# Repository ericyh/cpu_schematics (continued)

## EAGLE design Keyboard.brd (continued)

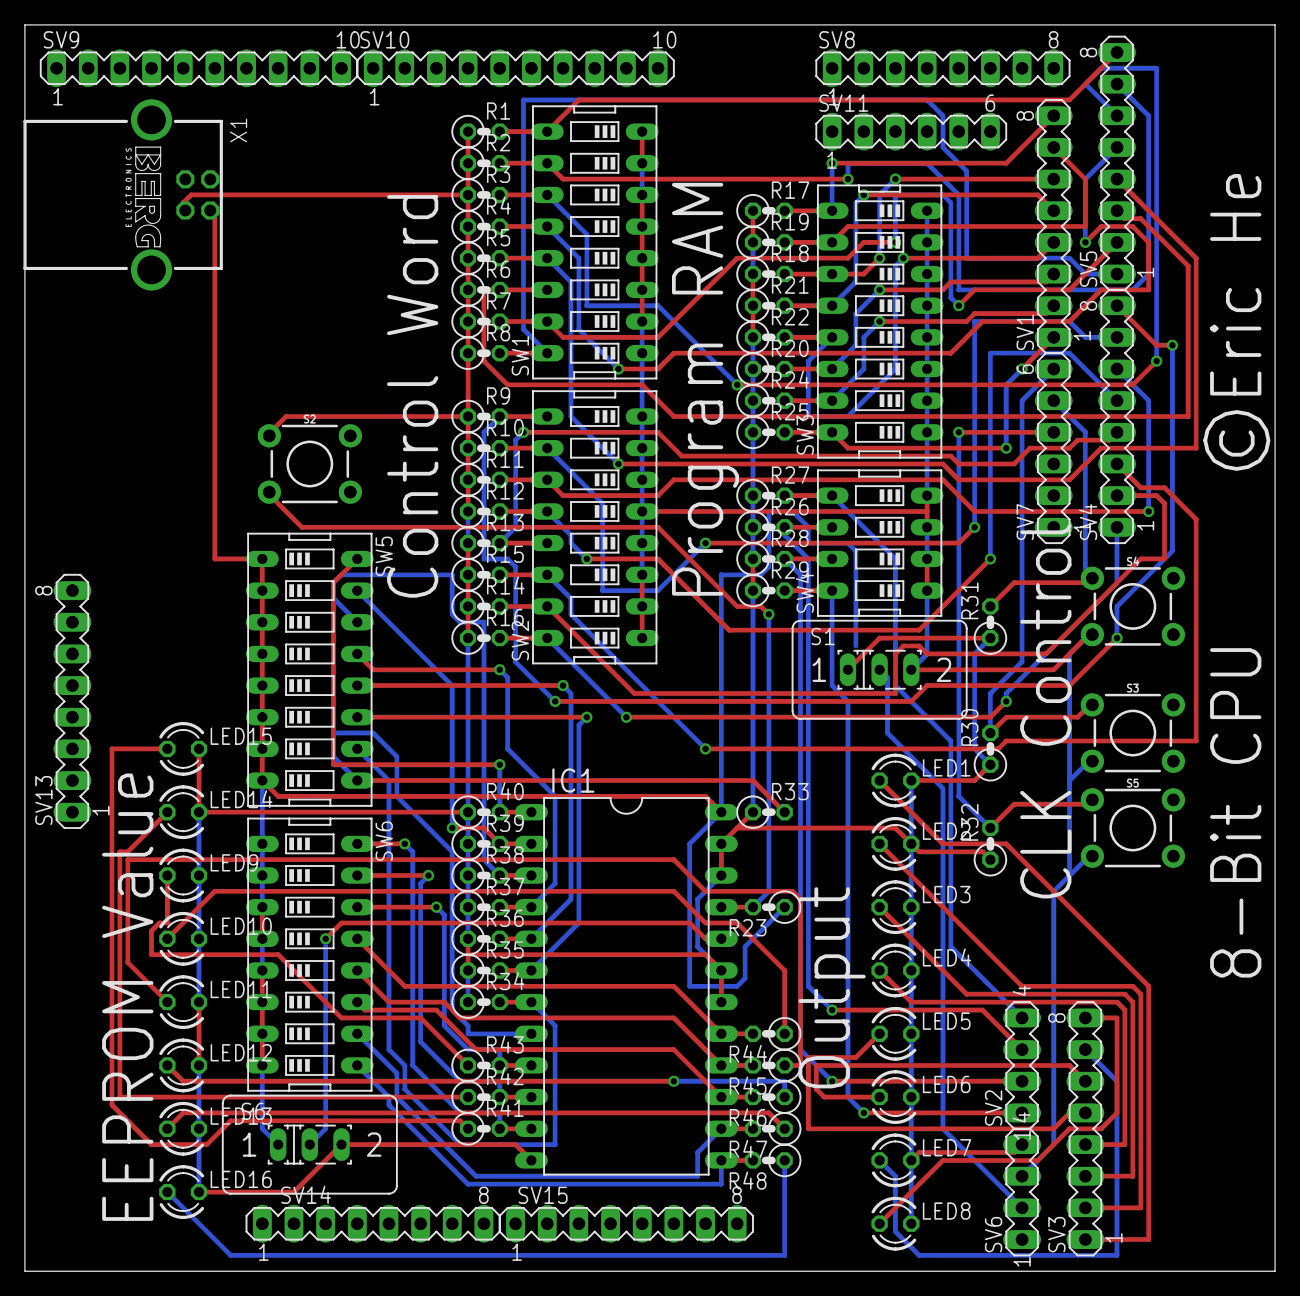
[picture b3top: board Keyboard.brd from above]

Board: 2 copper layers, 100.3 x 100.0 mm, 92 parts (0 on the bottom side), 68 nets.

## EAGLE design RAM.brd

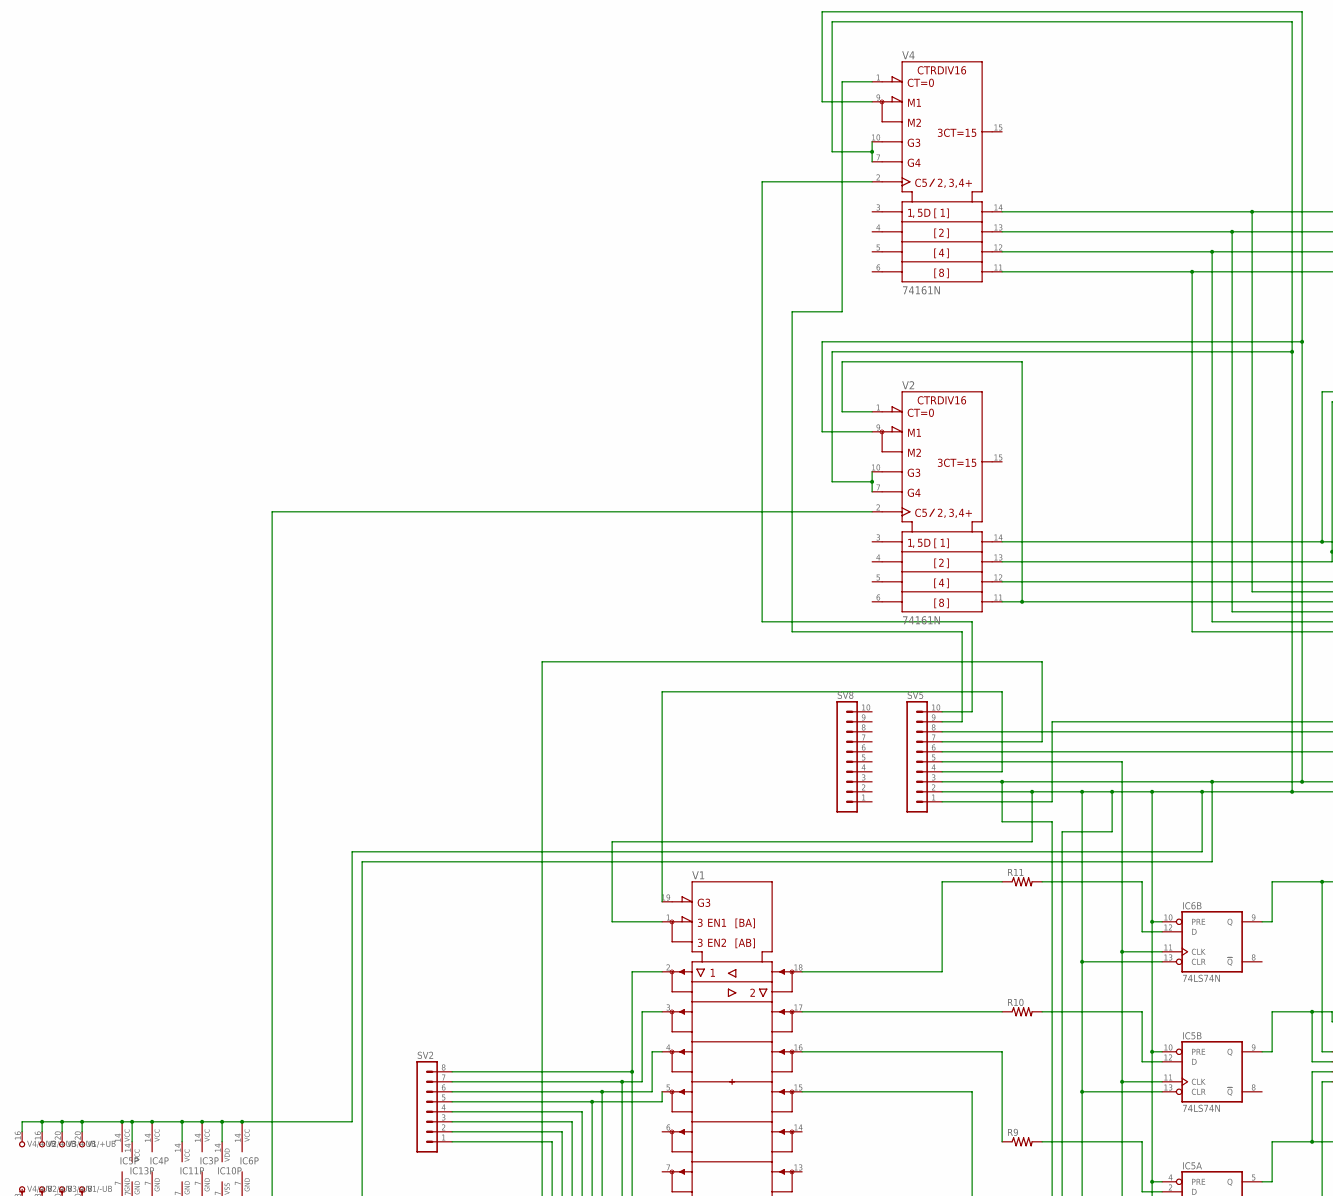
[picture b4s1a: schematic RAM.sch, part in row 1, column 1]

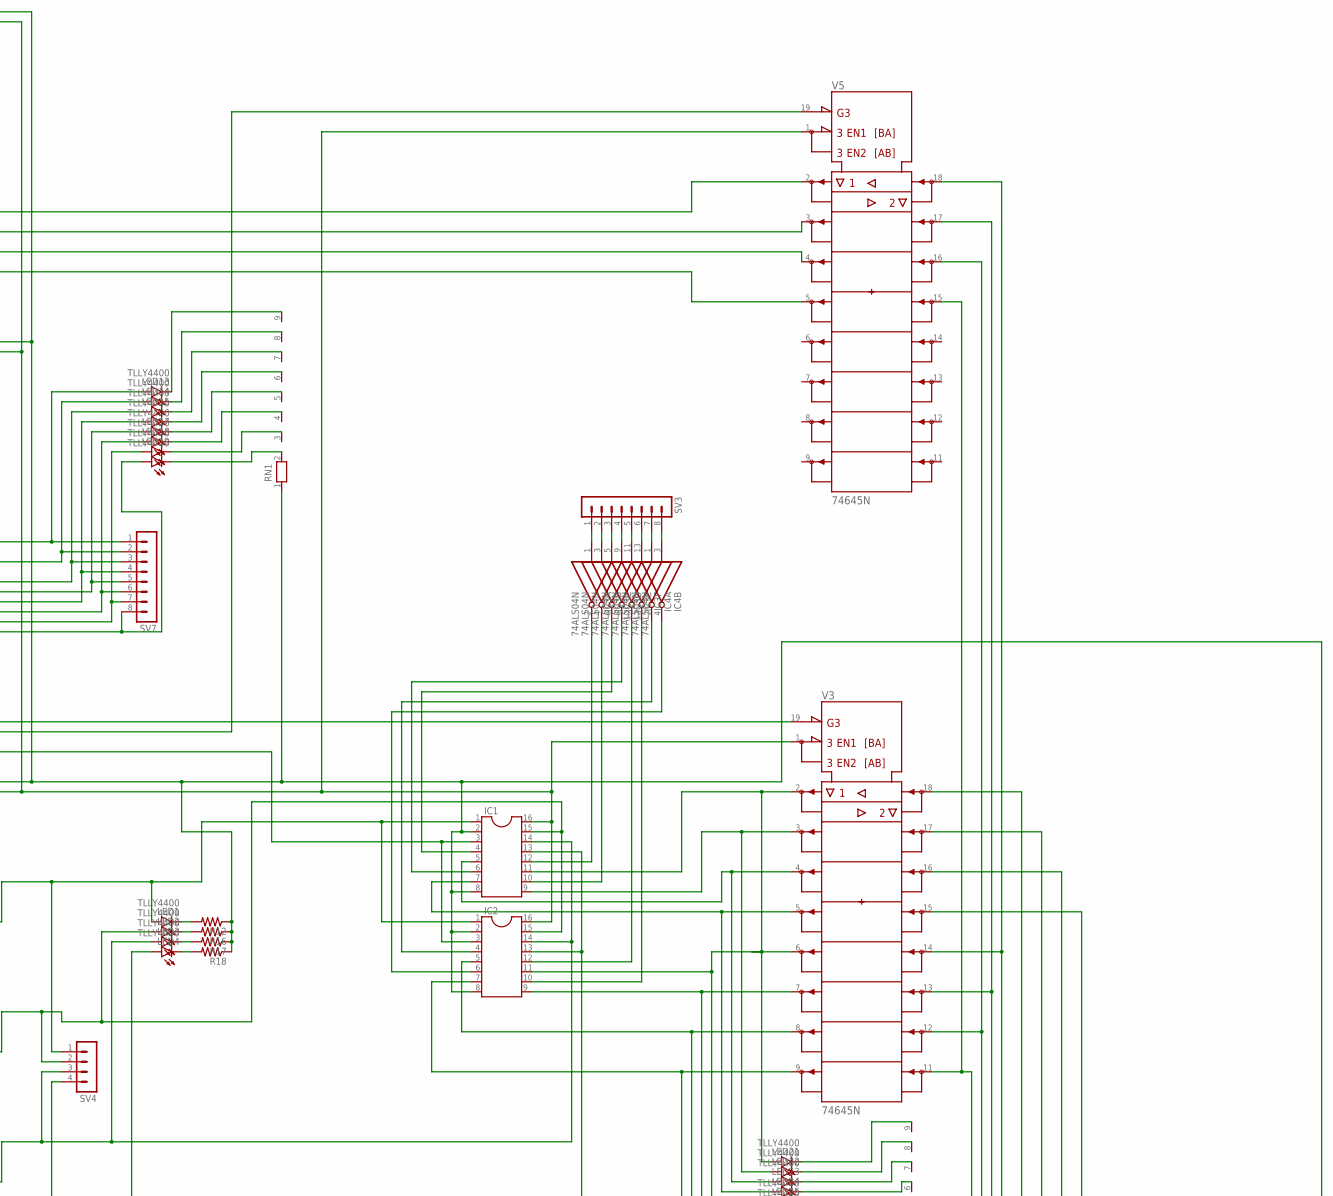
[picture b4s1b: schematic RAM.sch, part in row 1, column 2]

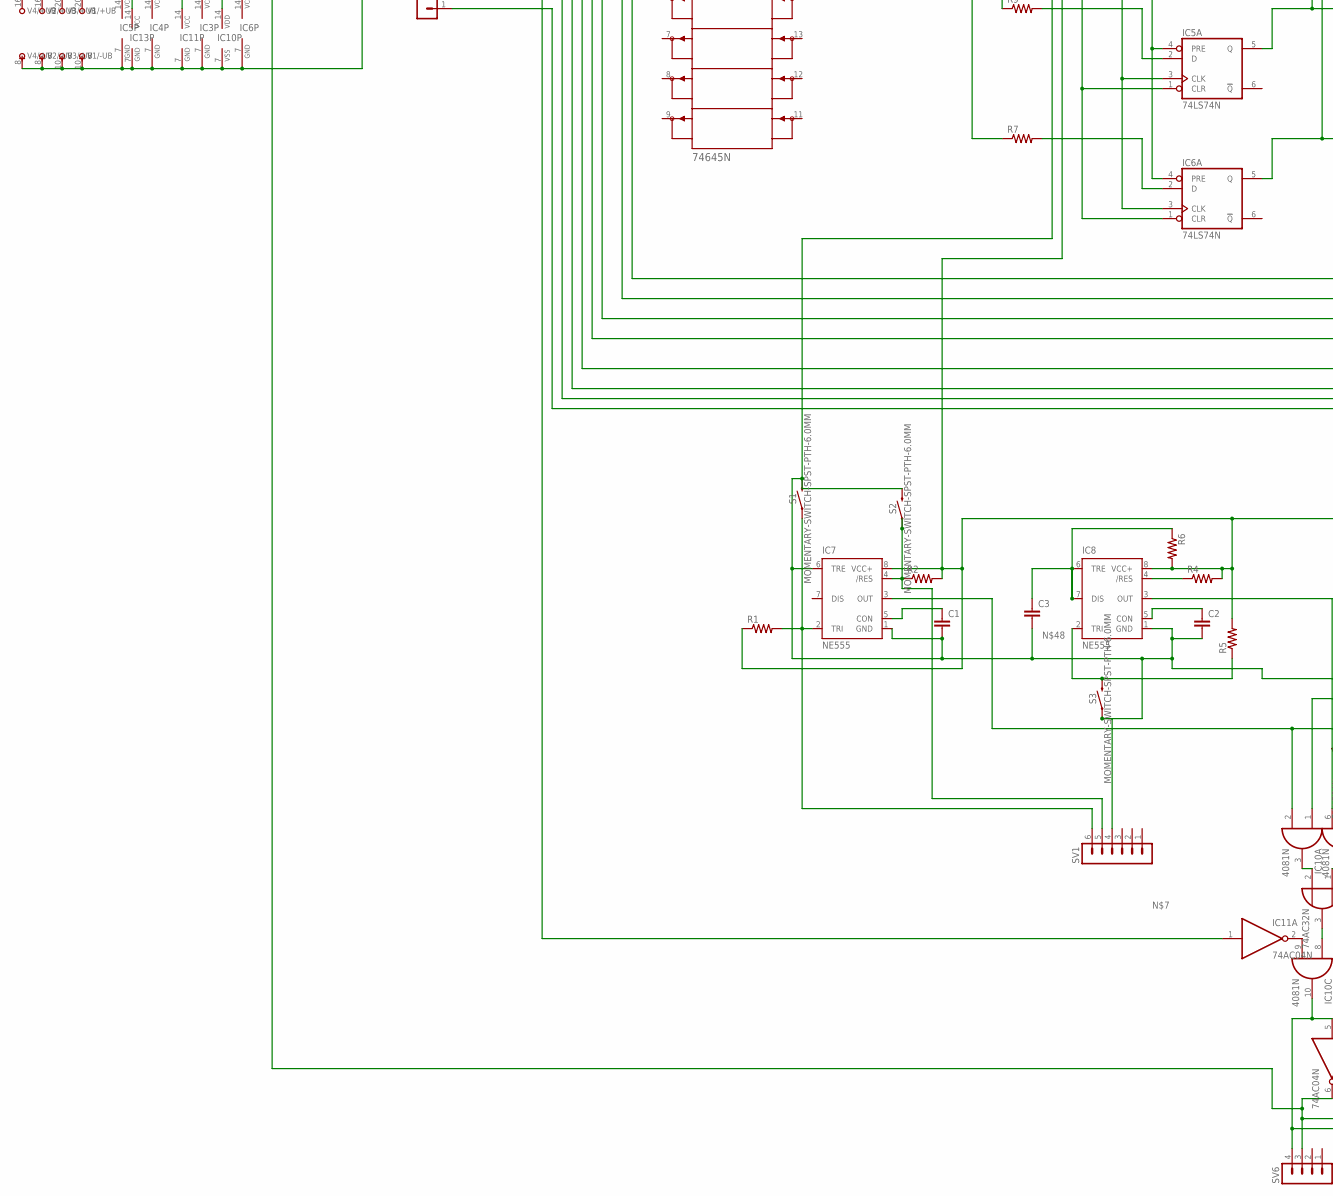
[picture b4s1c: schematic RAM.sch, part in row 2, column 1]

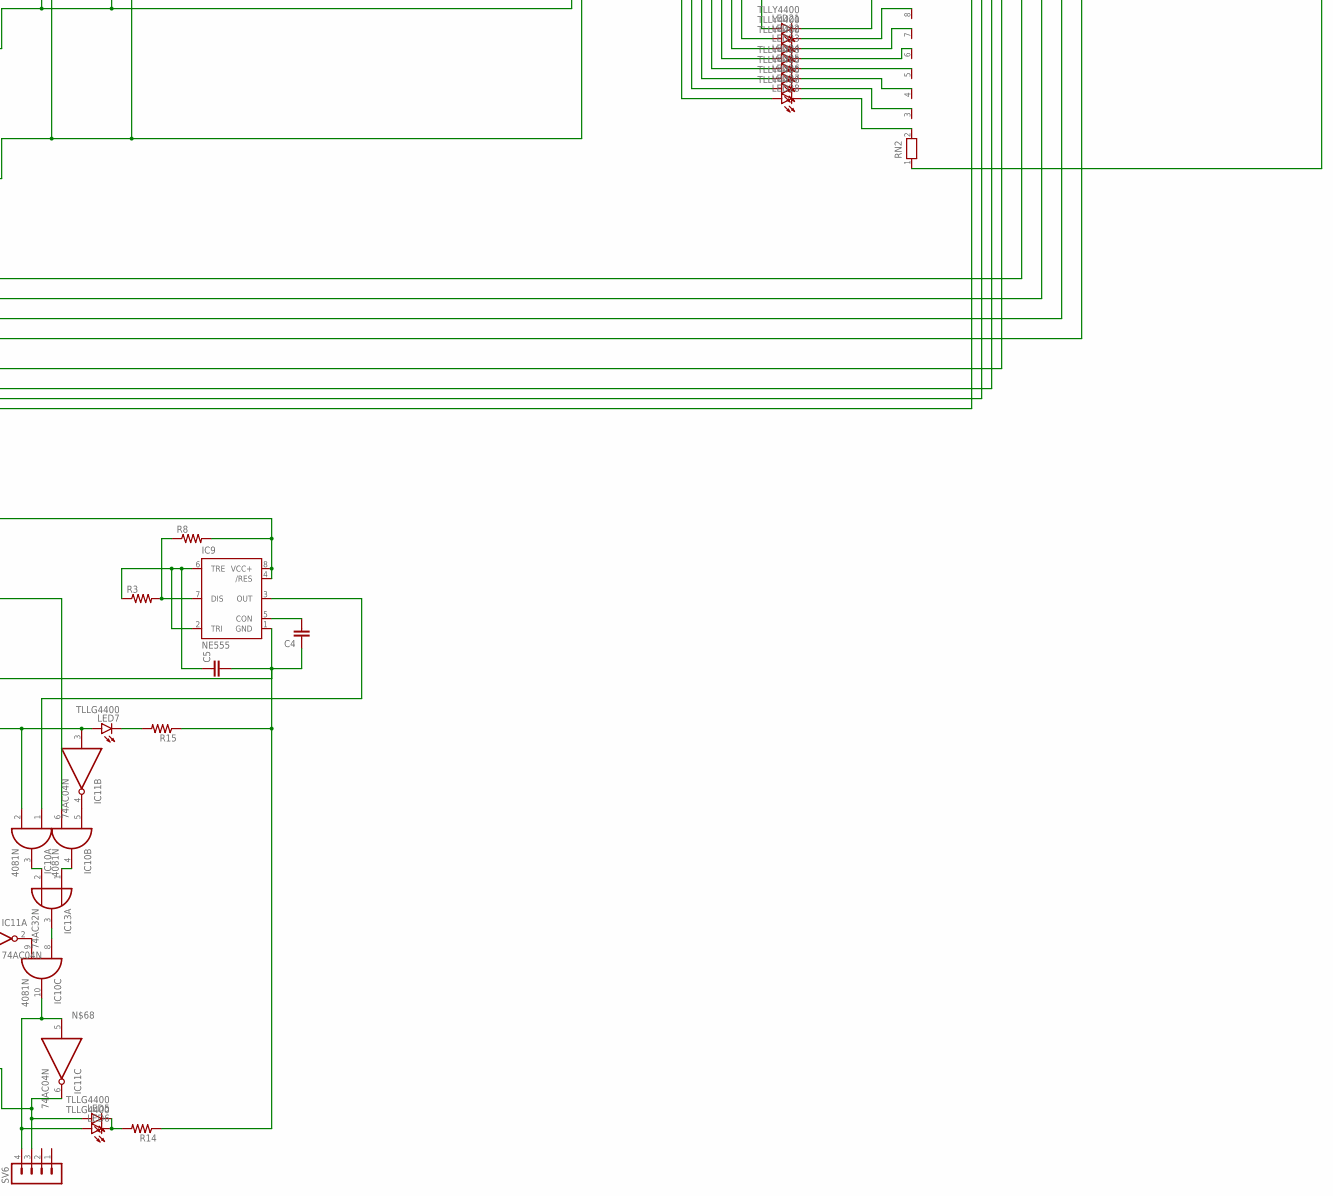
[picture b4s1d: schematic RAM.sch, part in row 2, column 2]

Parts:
C1, C2, C3, C4, C5: C2,5-3; C2.5-3
IC1, IC2: DIL16
IC3, IC4: 74ALS04N; DIL14
IC5, IC6: 74LS74N; DIL14
IC7, IC8, IC9: NE555; DIL-08
IC10: 4081N; DIL14
IC11: 74AC04N; DIL14
IC13: 74AC32N; DIL14
LED1, LED2, LED3, LED4, LED13, LED14, LED15, LED16, LED17, LED18, LED19, LED20, LED21, LED22, LED23, LED24, LED25, LED26, LED27, LED28: TLLY4400; LED3MM
LED5, LED6, LED7: TLLG4400; LED3MM
R1, R2, R3, R4, R5, R6, R7, R8, R9, R10, R11, R12, R14, R15, R16, R17, R18: R-US_0411/3V; 0411V
RN1, RN2: RN08; RN-9
S1, S2, S3: MOMENTARY-SWITCH-SPST-PTH-6.0MM; TACTILE_SWITCH_PTH_6.0MM
SV1: MA06-1
SV2, SV3, SV7: MA08-1
SV4, SV6: MA04-1
SV5, SV8: MA10-1
V1, V3, V5: 74645N; DIL20
V2, V4: 74161N; DIL16

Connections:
+UB: V5.20 (+UB)
-UB: V5.10 (-UB)
unnamed: LED28.K (C), RN2.2
unnamed: IC1.10, IC3.4 (O)
unnamed: IC1.1, IC2.1, IC6.9 (Q), LED1.A, SV4.1
unnamed: IC1.15, IC2.15, IC5.9 (Q), LED2.A, SV4.2
unnamed: C1.1, IC7.5 (CON)
unnamed: LED19.A, SV7.7, V4.12 (QC), V5.4 (A3)
unnamed: IC11.1 (I), SV5.7
unnamed: IC7.2 (TRI), R1.2, S1.1, SV1.6
unnamed: IC1.4, IC3.6 (O)
unnamed: SV2.8, V1.2 (A1), V3.18 (B1)
unnamed: IC1.3, IC2.3, SV5.6
unnamed: IC1.5, LED23.A, V3.4 (A3)
unnamed: IC1.7, LED24.A, V3.5 (A4)
unnamed: IC2.4, IC4.2 (O)
unnamed: IC2.10, IC3.12 (O)
unnamed: IC2.5, LED27.A, V3.8 (A7)
unnamed: IC2.7, LED28.A, V3.9 (A8)
unnamed: IC1.11, IC2.11, LED21.A, LED25.A, V3.2 (A1)
unnamed: IC5.3 (CLK), IC5.11 (CLK), IC6.3 (CLK), IC6.11 (CLK), SV5.5
unnamed: IC1.9, LED22.A, V3.3 (A2)
unnamed: IC1.6, IC3.8 (O)
unnamed: R10.1, V1.17 (B2)
unnamed: IC2.12, IC3.10 (O)
unnamed: R11.1, V1.18 (B1)
unnamed: R7.1, V1.15 (B4)
unnamed: IC6.12 (D), R11.2
unnamed: IC1.13, IC2.13, IC6.5 (Q), LED4.A, SV4.4
unnamed: IC2.6, IC4.4 (O)
unnamed: LED18.K (C), RN1.4
unnamed: LED20.K (C), RN1.2
unnamed: SV5.1, V3.19 (!G)
unnamed: IC3.1 (I), SV3.1
unnamed: IC3.3 (I), SV3.2
unnamed: IC3.5 (I), SV3.3
unnamed: IC3.9 (I), SV3.4
unnamed: IC3.11 (I), SV3.5
unnamed: C1.2, C2.2, C3.2, C4.1, C5.2, IC1.2, IC1.8, IC2.2, IC2.8, IC3.7 (GND), IC4.7 (GND), IC5.7 (GND), IC6.7 (GND), IC7.1 (GND), IC7.6 (TRE), IC8.1 (GND), IC9.1 (GND), IC10.7 (VSS), IC11.7 (GND), IC13.7 (GND), R12.1, R14.1, R15.1, R16.1, R17.1, R18.1, RN1.1, RN2.1, S1.3 (2), S2.3 (2), S3.1, SV1.4, SV5.3, V1.10 (-UB), V2.8 (-UB), V2.9 (!LOAD), V3.10 (-UB), V4.8 (-UB), V4.9 (!LOAD)
unnamed: IC3.13 (I), SV3.6
unnamed: C3.1, IC8.6 (TRE), IC8.7 (DIS), R6.1
unnamed: IC4.1 (I), SV3.7
unnamed: IC4.3 (I), SV3.8
unnamed: IC7.4 (/RES), R2.1, S2.1, SV1.5
unnamed: IC7.3 (OUT), IC10.2 (I1), IC11.3 (I), LED7.A
unnamed: C2.1, IC8.5 (CON)
unnamed: SV5.4, V1.19 (!G)
unnamed: IC10.4 (O), IC13.1 (I0)
unnamed: IC8.2 (TRI), R5.1, S3.3 (2)
unnamed: R9.1, V1.16 (B3)
unnamed: SV2.1, V3.11 (B8), V5.15 (B4)
unnamed: SV2.2, V3.12 (B7), V5.16 (B3)
unnamed: SV2.3, V3.13 (B6), V5.17 (B2)
unnamed: SV2.4, V3.14 (B5), V5.18 (B1)
unnamed: LED18.A, SV7.6, V4.13 (QB), V5.3 (A2)
unnamed: LED20.A, SV7.8, V4.11 (QD), V5.5 (A4)
unnamed: LED17.A, SV7.5, V4.14 (QA), V5.2 (A1)
unnamed: SV5.8, V5.19 (!G)
unnamed: IC8.3 (OUT), IC10.6 (I1)
unnamed: C5.1, IC9.2 (TRI), IC9.6 (TRE), R3.1
unnamed: IC1.14, IC2.14, IC5.5 (Q), LED3.A, SV4.3
unnamed: IC9.7 (DIS), R3.2, R8.1
unnamed: C4.2, IC9.5 (CON)
unnamed: LED5.K (C), LED6.K (C), R14.2
unnamed: IC9.3 (OUT), IC10.1 (I0)
unnamed: IC10.9 (I1), IC11.2 (O)
unnamed: IC10.5 (I0), IC11.4 (O)
unnamed: IC11.6 (O), LED5.A, SV6.3, V2.2 (CLK)
unnamed: IC10.10 (O), IC11.5 (I), LED6.A, SV6.4
unnamed: SV2.7, V1.3 (A2), V3.17 (B2)
unnamed: LED13.A, SV7.1, V2.14 (QA)
unnamed: LED14.A, SV7.2, V2.13 (QB)
unnamed: LED15.A, SV7.3, V2.12 (QC)
unnamed: LED16.A, SV7.4, V2.1 (!CLR), V2.11 (QD)
unnamed: IC10.8 (I0), IC13.3 (O)
unnamed: SV2.6, V1.4 (A3), V3.16 (B3)
unnamed: IC10.3 (O), IC13.2 (I1)
unnamed: SV2.5, V1.5 (A4), V3.15 (B4)
unnamed: IC1.16, IC2.16, IC3.14 (VCC), IC4.14 (VCC), IC5.1 (CLR), IC5.4 (PRE), IC5.10 (PRE), IC5.13 (CLR), IC5.14 (VCC), IC6.1 (CLR), IC6.4 (PRE), IC6.10 (PRE), IC6.13 (CLR), IC6.14 (VCC), IC7.8 (VCC+), IC8.8 (VCC+), IC9.4 (/RES), IC9.8 (VCC+), IC10.14 (VDD), IC11.14 (VCC), IC13.14 (VCC), R1.1, R2.2, R4.2, R5.2, R6.2, R8.2, SV5.2, V1.1 (DIR), V1.20 (+UB), V2.7 (ENP), V2.10 (ENT), V2.16 (+UB), V3.1 (DIR), V3.20 (+UB), V4.7 (ENP), V4.10 (ENT), V4.16 (+UB), V5.1 (DIR)
unnamed: IC8.4 (/RES), R4.1
unnamed: LED19.K (C), RN1.3
unnamed: SV5.9, V4.1 (!CLR)
unnamed: SV5.10, V4.2 (CLK)
unnamed: IC1.12, IC3.2 (O)
unnamed: IC2.9, LED26.A, V3.7 (A6)
unnamed: LED17.K (C), RN1.5
unnamed: LED16.K (C), RN1.6
unnamed: LED15.K (C), RN1.7
unnamed: LED14.K (C), RN1.8
unnamed: LED13.K (C), RN1.9
unnamed: LED7.K (C), R15.2
unnamed: LED27.K (C), RN2.3
unnamed: LED26.K (C), RN2.4
unnamed: LED25.K (C), RN2.5
unnamed: LED24.K (C), RN2.6
unnamed: LED23.K (C), RN2.7
unnamed: LED22.K (C), RN2.8
unnamed: LED21.K (C), RN2.9
unnamed: LED1.K (C), R12.2
unnamed: LED2.K (C), R16.2
unnamed: LED3.K (C), R17.2
unnamed: LED4.K (C), R18.2
unnamed: IC5.12 (D), R10.2
unnamed: IC5.2 (D), R9.2
unnamed: IC6.2 (D), R7.2

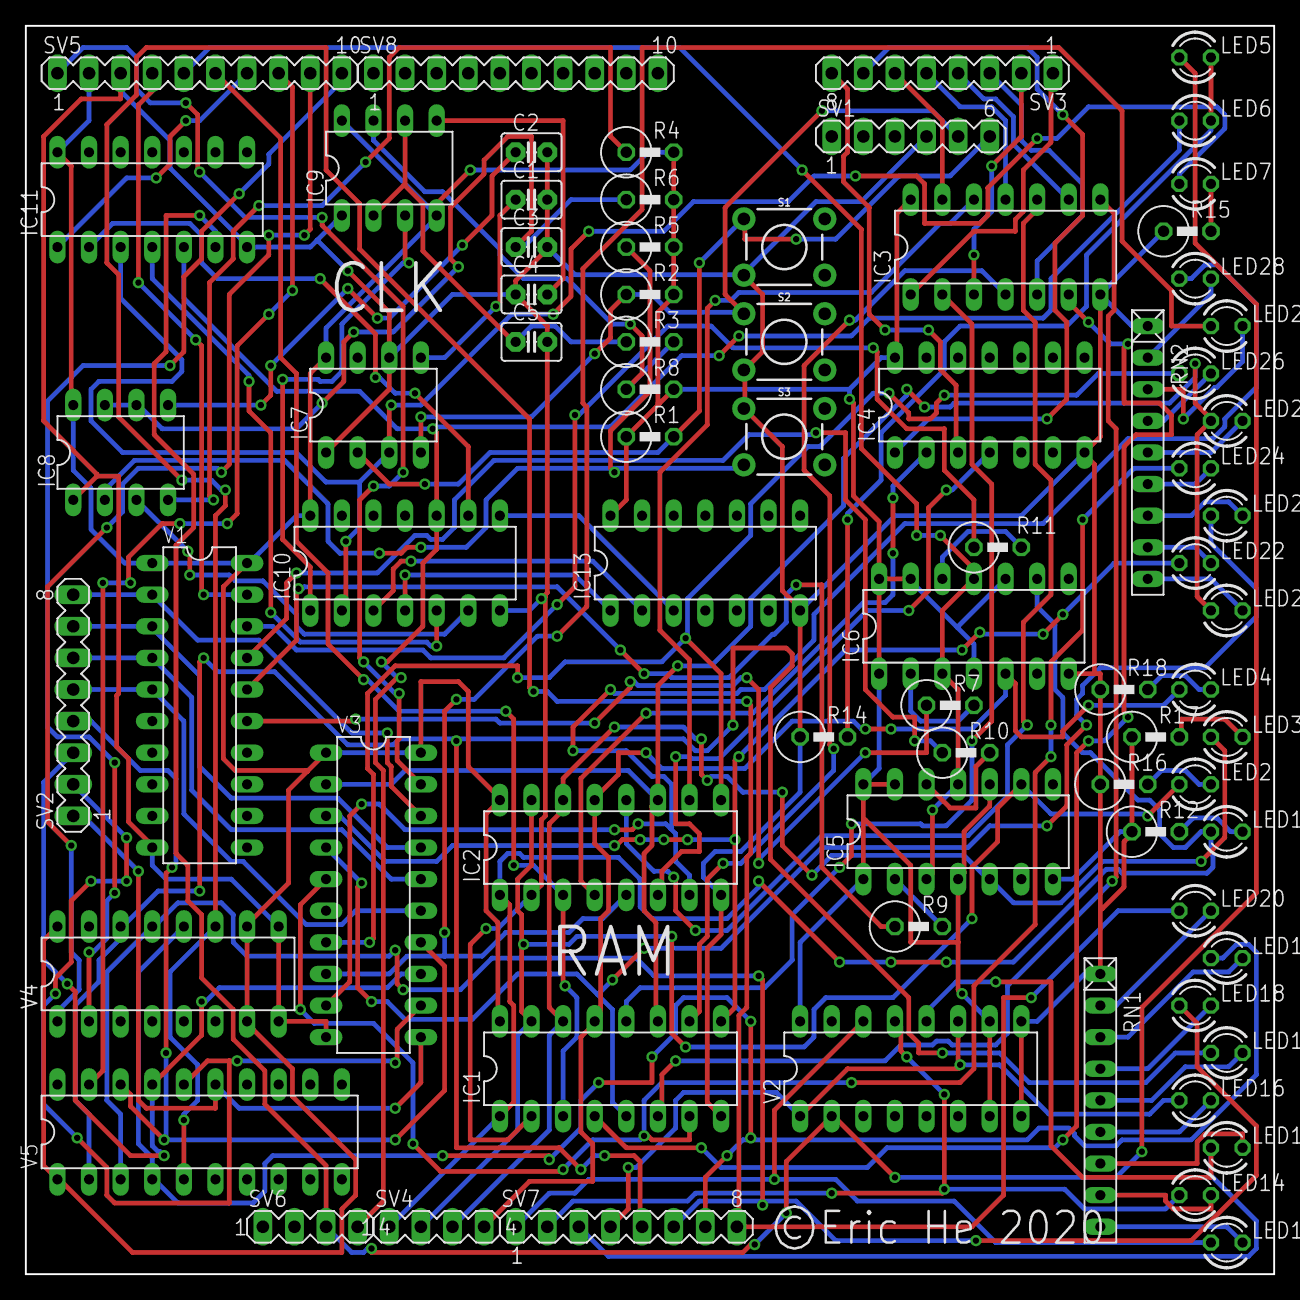
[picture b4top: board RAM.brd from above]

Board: 2 copper layers, 100.3 x 100.3 mm, 75 parts (0 on the bottom side), 103 nets.
